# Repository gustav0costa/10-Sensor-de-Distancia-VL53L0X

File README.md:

# Github criado para as disciplinas de Sistemas Embarcados e Tecnicas de Prototipagem.

# ######################
# Tecnicas de Prototipagem:      
#  - Caio Eduardo      
#  - Claudio Alberto   
#  - Gustavo Diego     
# #####################

# #######################
# Sistemas Embarcados: 
#  - Alisson Lucena      
#  - Caio Eduardo        
#  - Gustavo Diego       
# #######################

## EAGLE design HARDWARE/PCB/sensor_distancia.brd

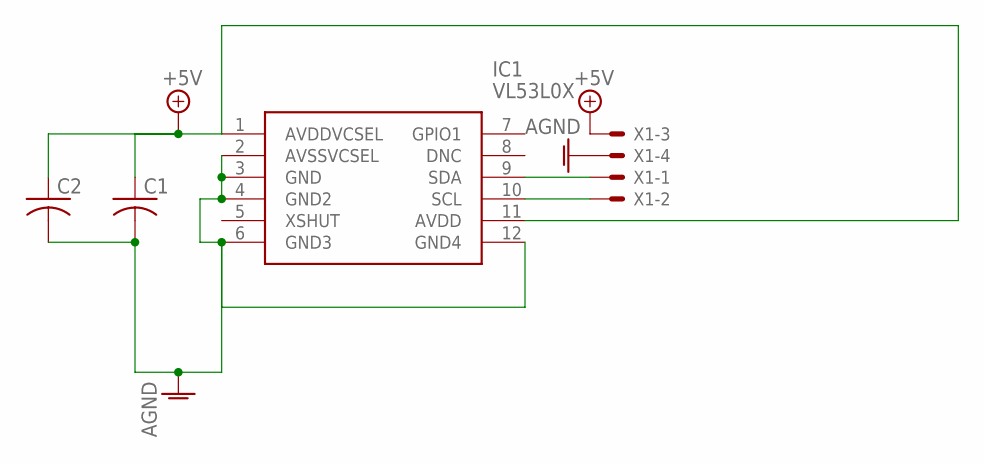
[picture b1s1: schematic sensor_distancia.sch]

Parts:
C1, C2: C-US025-025X050; C025-025X050
IC1: VL53L0X
X1: KK-156-4

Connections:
+5V: C1.1, C2.1, IC1.1 (AVDDVCSEL), IC1.11 (AVDD), X1.3
AGND: C1.2, C2.2, IC1.2 (AVSSVCSEL), IC1.3 (GND), IC1.4 (GND2), IC1.6 (GND3), IC1.12 (GND4), X1.4
unnamed: IC1.10 (SCL), X1.2
unnamed: IC1.9 (SDA), X1.1

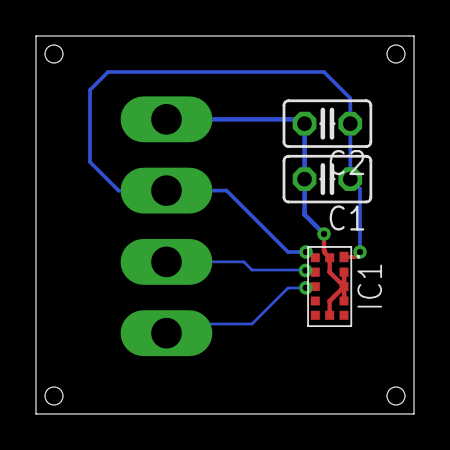
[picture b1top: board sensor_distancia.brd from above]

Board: 2 copper layers, 21.0 x 21.0 mm, 4 parts (1 on the bottom side), 4 nets.

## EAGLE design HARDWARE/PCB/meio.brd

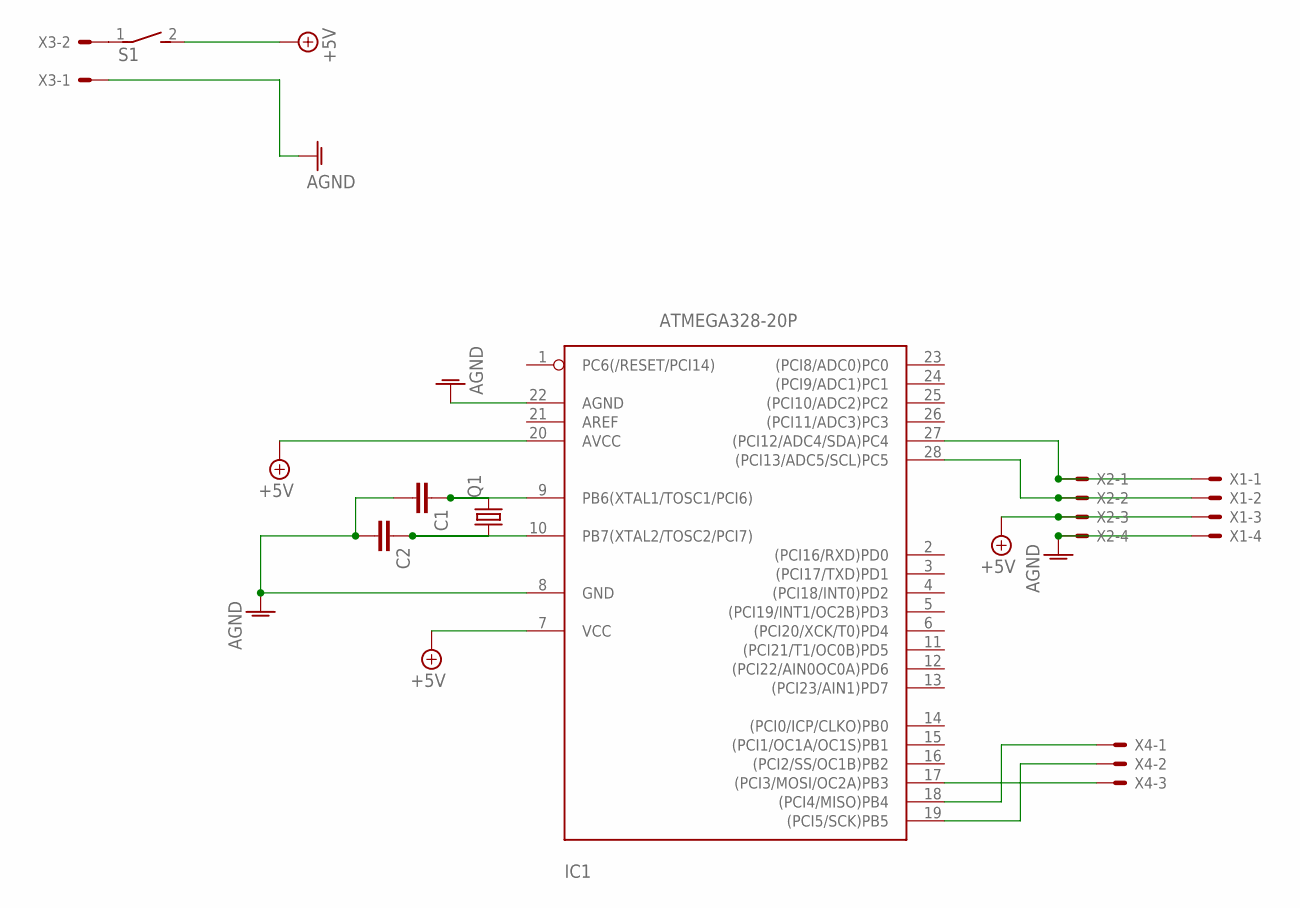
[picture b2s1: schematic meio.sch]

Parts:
C1, C2: C-EU025-025X050; C025-025X050
IC1: ATMEGA328-20P; DIL28-3
Q1: CRYSTALHC49S; HC49/S
S1: DS01E; DS-01
X1, X2: KK-156-4
X3: KK-156-2
X4: KK-156-3

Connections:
+5V: IC1.7 (VCC), IC1.20 (AVCC), S1.2, X1.3, X2.3
AGND: C1.2, C2.2, IC1.8 (GND), IC1.22 (AGND), X1.4, X2.4, X3.1
unnamed: C1.1, IC1.9 (PB6(XTAL1/TOSC1/PCI6)), Q1.2
unnamed: C2.1, IC1.10 (PB7(XTAL2/TOSC2/PCI7)), Q1.1
unnamed: IC1.27 ((PCI12/ADC4/SDA)PC4), X1.1, X2.1
unnamed: IC1.28 ((PCI13/ADC5/SCL)PC5), X1.2, X2.2
unnamed: S1.1, X3.2
unnamed: IC1.18 ((PCI4/MISO)PB4), X4.1
unnamed: IC1.19 ((PCI5/SCK)PB5), X4.2
unnamed: IC1.17 ((PCI3/MOSI/OC2A)PB3), X4.3

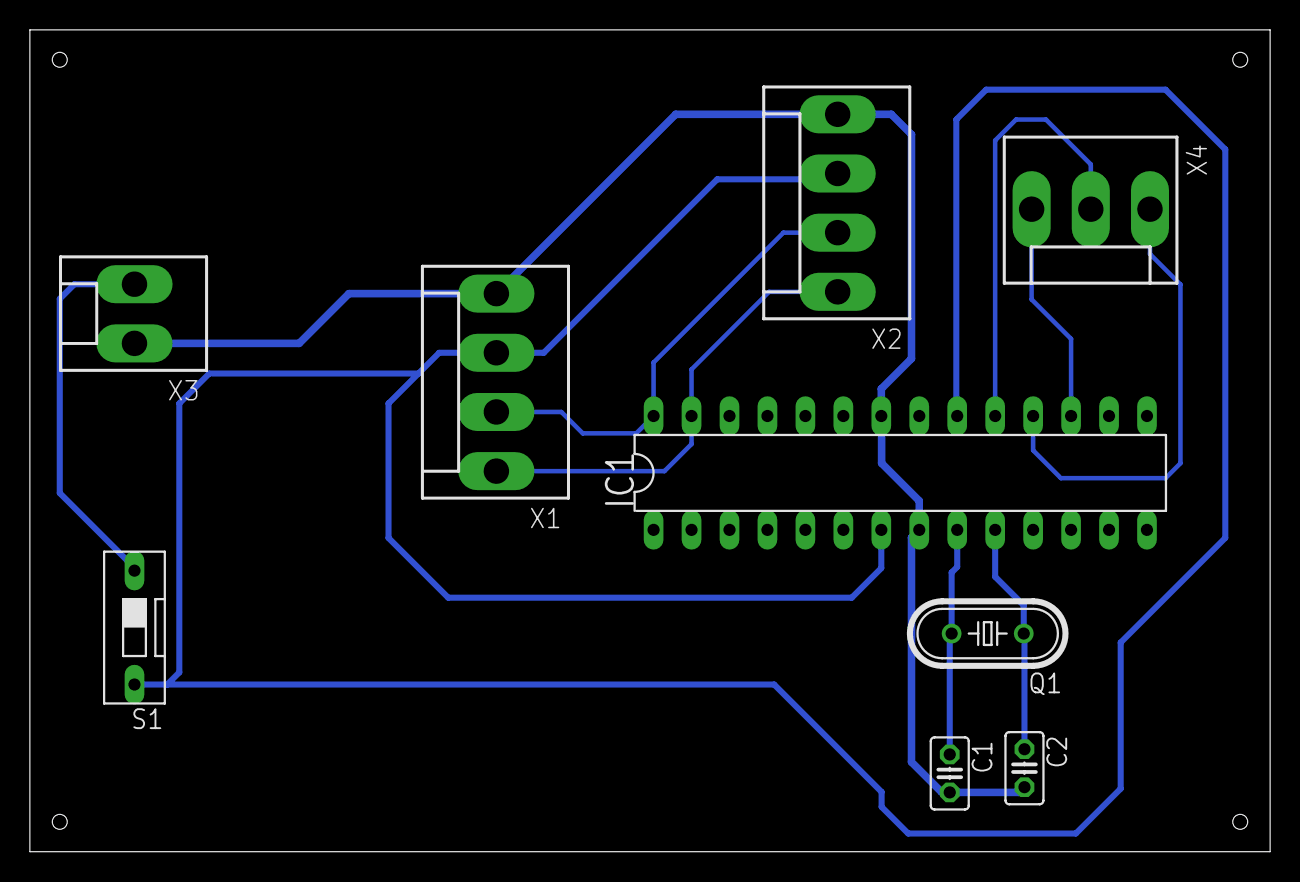
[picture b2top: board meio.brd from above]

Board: 2 copper layers, 83.0 x 55.0 mm, 9 parts (0 on the bottom side), 10 nets.

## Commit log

2021-07-30 Create Docs
2021-07-30 Create teste
2021-07-30 Update and rename teste to README
2021-07-30 Rename README to README.md
2021-08-04 Rename Docs/README.md to README1.md
2021-08-04 Rename README1.md to README.md
2021-09-25 Projeto Trena
2021-10-05 Prototipagem
